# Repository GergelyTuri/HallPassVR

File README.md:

# HallPassVR
## Virtual reality system for head-fixed mouse experiments. 

See published paper on [JOVE](https://app.jove.com/v/64863/an-open-source-virtual-reality-system-for-the-measurement-of-spatial-learning-in-head-restrained-mice).

We developed an inexpensive, single board computer-based, easy-to-use setup for investigation of mouse spatial learning behavior using a visual virtual reality (VR) environment. This system uses a network of microcontrollers (ESP32) and a Raspberry Pi single-board computer to display a virtual linear track to a headfixed mouse running on a wheel. Along with a custom software package written in Python and C++ to generate parameterized virtual environments, this methodology allows researchers the design of various spatial navigation-based experiments to study neural circuits in the brain underlying spatial behaviors. [Example video here](https://www.youtube.com/watch?v=iCfhJT3dYIo):  

## Main hardware requirements: 
1. _ESP32 microcontrollers_ to track and convert mouse movement on a treadmill or wheel to serial data and to control other harware elements (lick spout for reward delivery).
2. _Raspberry Pi 4_ for building and simulating the virtual reality environment. 
3. _Projector_ for visualizing the virtual corridor.
4. PCB shields through [OpenMaze](https://claylacefield.wixsite.com/openmazehome/openmaze-shields)

## Software requirements: 
1. The virtual corridor was designed with _Python_. 
2. Native, Linux-based OS for Raspberry Pi.
3. _tkinter_ was used for designing the graphical user interface.
4. _Arduino IDE_ for programing the microcontrollers.
5. _Processing_ for data collection and plotting.
6. The analysis of behavior files currently requires _Matlab_.

### What we have done: 
1. We built the main part of the system which can simultaneously run and show the virtual reality environment on a computer display and a projector.
2. We have built a prototype GUI which can be used to build virtual corridors from virtually any kind of jpeg images.
3. We tested the system with several testbenches.

### Work in progress: 
1. Finalizing the code by adding documentation and examples.
                
### Future plans: 
1. Optimization of the system by e.g., adding an RFID sensor to increase wheel tracking accuracy.
3. Adding other features to the VR software like naturalistic scenes, looming stimulus or cliff-like effects. 
4. Implementing the analysis scripts in Python.
5. Increasing the flexibility of the existing protocols. 
6. Implementing a wireless (e.g., bluetooth) system using this platform.
## Quickstart:
### Initializing VR environment: 

1. Open a terminal window in Raspberry Pi and navigate to the `HallPassVR` folder
 ```bash
cd /home/pi/Documents/HallPassVR
 ```
2. Starting the VR GUI:
```bash
python3 HallPassVR_GUI.py
 ```
3. Setting up the floors and corridors in the GUI
4. Setting up `Processing` sketch to acquire and plot behavior.
5. Preliminary analysis of the acquired data can be done in Matlab with the scripts in `/Analysis code` folder.

#### GUI: 

#### Example virtual corridor: 

For feature requests, support or questions, please open a ticket on [GitHub](https://github.com/GergelyTuri/mouseVR/issues).

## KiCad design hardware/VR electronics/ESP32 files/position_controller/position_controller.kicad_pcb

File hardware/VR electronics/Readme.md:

# Instructions for the electronic components

Files in the `ESP32 files` directory should be uploaded to the ESP32 boards connected to the lickport and rotary encoder. 

Files in `/PCBs` can get manufatured with companies specialized to PCB production. Typically we use [OSH Park](https://oshpark.com/) if we don't want to modify the design. More info on how to order and assemble these shields can be found on [OpenMaze](http://www.openmaze.org/).

| material | description | source |
| -------- | ----------- | ------ |
| Raspberry Pi 4 model B | single-board computer | e.g., raspberrypi.com, adafruit.com |
| rotary encoder | ENS1J-B28-L00256L | digikey.com[^1] |
|ESP32 devKitC v4 | microcontroller (x2)| e.g., [Amazon.com](https://www.amazon.com/s?k=ESP32&crid=ZCZ3J597DJO9&sprefix=esp32%2Caps%2C94&ref=nb_sb_noss_1)|
|OpenMaze OMwESP32 shield| custom design | see: `/PCBs` folder |

[^1]: Alternative sources: amazon.com, mouser.com, DigiPart, etc.

## Installation instructions for Raspberry Pi:
### Configure RaspberryPi 4 model B 
This single-board computer has an onboard GPU to facilitate VR environment rendering, as well as two HDMI ports for experiment control/monitoring and VR projection.
1. Download Raspberry Pi Imager app and install OS (currently RaspberryPi OS r.2021-05-07) on microSD card (8GB+), insert and boot Raspberry Pi.
2. Configure Raspberry Pi: (menu bar) 
- `Preferences>Raspberry Pi Configuration>`
  - `Display>Screen Blanking>Disable`
  - `Interfaces>Serial Port>Enable` 
  - `Performance>GPU Memory>256`
3. In the terminal: 
``` bash
sudo nano /boot/config.txt
``` 
then uncomment `config_hdmi_boost=4`. Save, reboot the Raspberry Pi.

4. Download and install Arduino IDE from arduino.cc/en/software (e.g. arduino-1.8.19-linuxarm.tar.gz)
5. Download and install Processing IDE from github.com/processing/processing4/releases (e.g. processing-4.0.1-linux-arm32.tgz)
6. In the terminal
```bash
sudo pip3 install pillow –-upgrade
```
7. Then, 
```bash
sudo pip3 install pi3d
```
8. Install ESP32 support on Arduino IDE.

## Set up rotary encoder-ESP32 connections
1. Connect wires between rotary encoder and ESP32.
2. Connect serial RX/TX wires between ESP32 Serial2 (pins 16,17) and behavior ESP32.
3. Connect serial RX/TX wires between ESP32 Serial0 (RX/TX) and Raspberry Pi GPIO (or direct USB connection).
4. Set up behavior ESP32 connections with behavioral hardware (via OMwESP32small PCB).
5. Connect 12V liquid solenoid valve to ULN2803 IC output (e.g. pin#32).
6. Connect lick port to ESP32 touch inputs (e.g. T2, GPIO15).
7. Connect serial RX/TX wires between behav ESP32 Serial2 (pins 16,17) and rotary encoder ESP32 (see above #1.b.).
8. Plug USB into Raspberry Pi USB port (or other PC running Processing to capture behavior data).
9. Plug Raspberry Pi HDMI #2 output into projector HDMI port.

## Set up software (rotary encoder ESP32 and behavior ESP32 w. OM PCB)
1. Plug rotary encoder ESP32 into Raspberry Pi USB port first- it will be automatically be named `/dev/ttyUSB0`
2. Load rotary encoder arduino code by first selecting the ESP32 under `Arduino IDE>Tools>Boards>ESP32 Dev Module`, then `Tools>Port`>`/dev/ttyUSB0`, then click `Upload`: `RotaryEncoder_Esp32_VR.ino`
3. Plug behavior ESP32 into Raspberry Pi USB port next- it will be named `/dev/ttyUSB1`
4. Load behavior sequence arduino code (ESP32 Dev Module already selected), then `Tools>Port>` `/dev/ttyUSB1`, then click `Upload`: `wheel_VR_behavior.ino`
5. You can test serial connections by selecting the Port in the Arduino IDE, then clicking on `Tools>Serial Monitor` (baud rate:115200), to observe serial output from the rotary board (USB0) or the behavior board (USB1).
6. Download HallPassVR python code from this GitHub repo (`/software/HallPassVR`) to `/home/pi/Documents`.

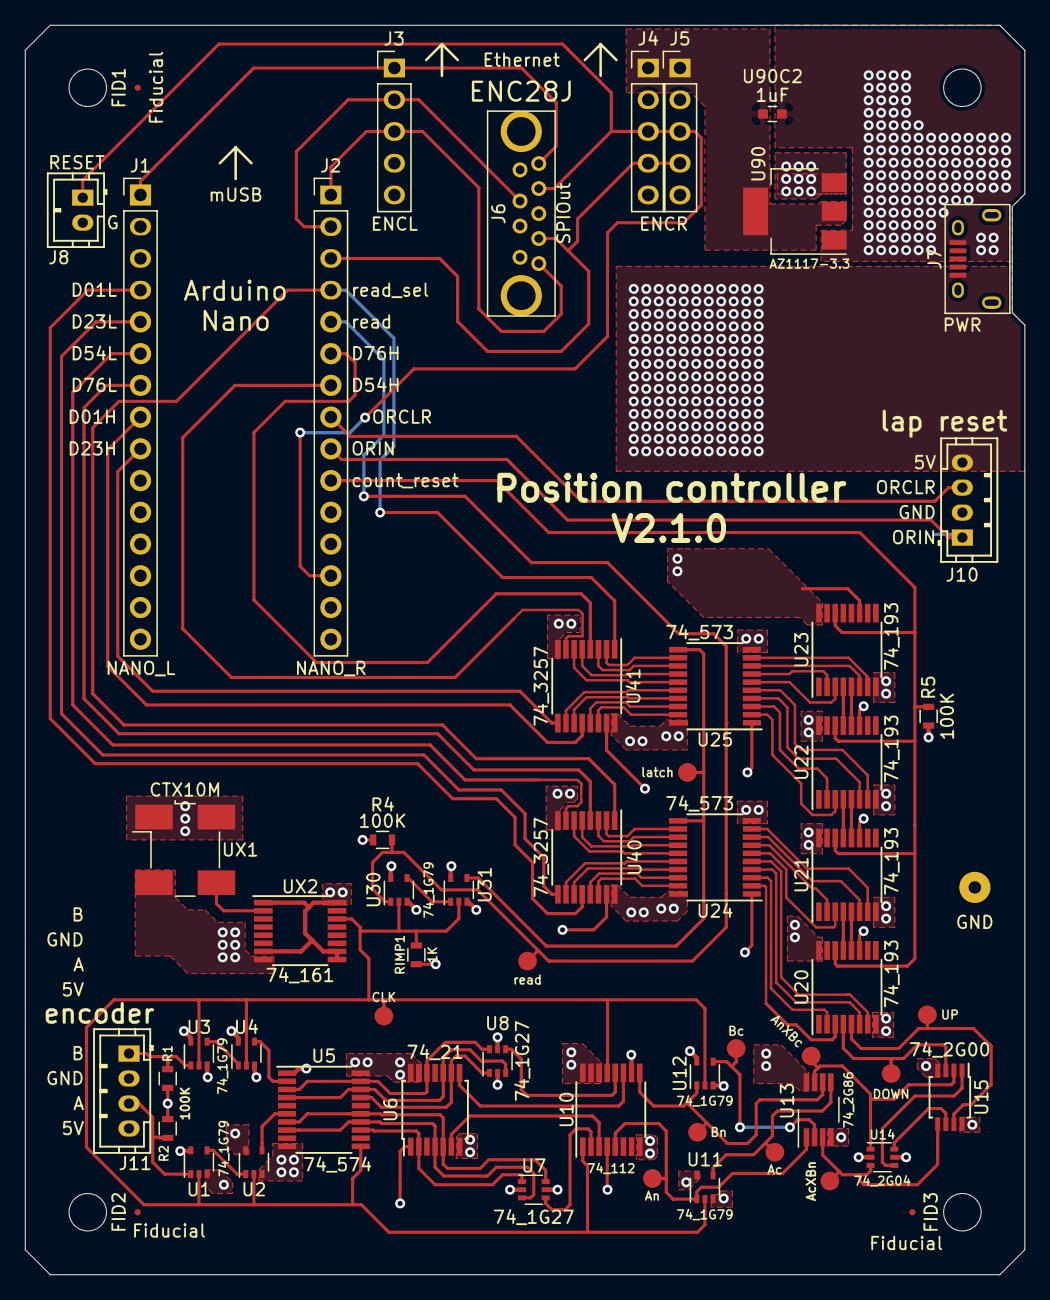
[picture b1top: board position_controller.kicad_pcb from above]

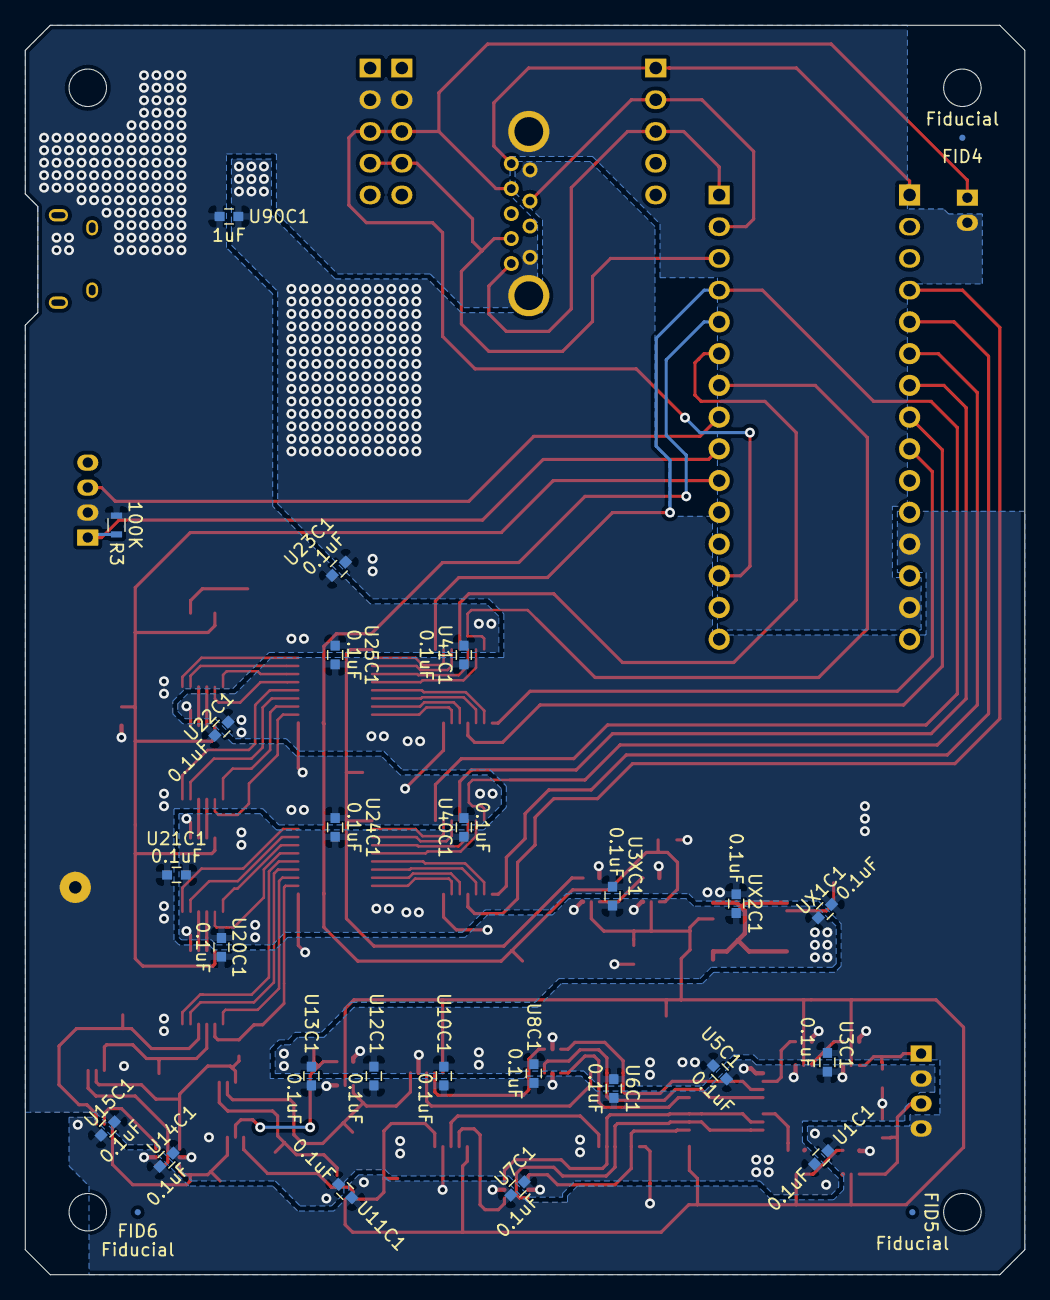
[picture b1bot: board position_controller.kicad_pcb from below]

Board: 2 copper layers, 80.0 x 100.0 mm, 86 parts (28 on the bottom side), 89 nets.

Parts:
FID1, FID2, FID3, FID4, FID5, FID6: Fiducial; Fiducial_0.5mm_Dia_1mm_Outer
J1: NANO_L; Pin_Header_Straight_1x15_Pitch2.54mm
J2: NANO_R; Pin_Header_Straight_1x15_Pitch2.54mm
J3: ENCL; Pin_Header_Straight_1x05_Pitch2.54mm
J4: ENCR; Pin_Header_Straight_1x05_Pitch2.54mm
J5: ENCRW; Pin_Header_Straight_1x05_Pitch2.54mm
J6: SPIOut; USB3_A_vertical_molex
J7: PWR; USB_Micro-B
J8: RESET; Connectors_JST_B2B-PH-K
J10: lap reset; Connectors_JST_B4B-PH-K
J11: encoder; Connectors_JST_B4B-PH-K
R1, R2, R3, R4, R5: 100K; R_0603
RIMP1: 1K; R_0603
TAc1: Ac; Measurement_Point_Round-SMD-Pad_Small
TAcXBn1: AcXBn; Measurement_Point_Round-SMD-Pad_Small
TAn1: An; Measurement_Point_Round-SMD-Pad_Small
TAnXBc1: AnXBc; Measurement_Point_Round-SMD-Pad_Small
TBc1: Bc; Measurement_Point_Round-SMD-Pad_Small
TBn1: Bn; Measurement_Point_Round-SMD-Pad_Small
TCLK1: CLK; Measurement_Point_Round-SMD-Pad_Small
TDN1: DOWN; Measurement_Point_Round-SMD-Pad_Small
TLatch1: latch; Measurement_Point_Round-SMD-Pad_Small
TPGND1: GND; Measurement_Point_Round-TH_Big
TRead1: read; Measurement_Point_Round-SMD-Pad_Small
TUP1: UP; Measurement_Point_Round-SMD-Pad_Small
U1, U2, U3, U4, U11, U12, U30, U31: 74_1G79; SOT-353_SC-70-5
U1C1, U3C1, U3XC1, U5C1, U6C1, U7C1, U8C1, U10C1, U11C1, U12C1, U13C1, U14C1, U15C1, U20C1, U21C1, U22C1, U23C1, U24C1, U25C1, U40C1, U41C1: 0.1uF; C_0603
U5: 74_574; TSSOP-20_4.4x6.5mm_Pitch0.65mm
U6: 74_21; TSSOP-14_4.4x5mm_Pitch0.65mm
U7, U8: 74_1G27; SOT-363_SC-70-6
U10: 74_112; TSSOP-16_4.4x5mm_Pitch0.65mm
U13: 74_2G86; VSSOP-8_3.0x3.0mm_Pitch0.65mm
U14: 74_2G04; SOT-363_SC-70-6
U15: 74_2G00; TSSOP-8_3x3mm_Pitch0.65mm
U20, U21, U22, U23: 74_193; TSSOP-16_4.4x5mm_Pitch0.65mm
U24, U25: 74_573; TSSOP-20_4.4x6.5mm_Pitch0.65mm
U40, U41: 74_3257; TSSOP-16_4.4x5mm_Pitch0.65mm
U90: AZ1117-3.3; SOT-223-3_TabPin2
U90C1, U90C2: 1uF; C_0603
UX1: CTX10M; Oscillator_SMD_Abracon_ASV-4pin_7.0x5.1mm_HandSoldering
UX1C1, UX2C1: 0.1uF; C_0603
UX2: 74_161; TSSOP-16_4.4x5mm_Pitch0.65mm

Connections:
+3V3: J4.1, J5.1, U90.2, U90C2.2
/A: J11.3, R2.1, U1.1
/AQ0: U5.7, U5.15, U6.5, U7.6
/AQ1: U5.8, U5.14, U6.4, U7.3
/AQ2: U5.13, U6.2, U7.1
/Ac: TAc1.1, U11.4, U13.5
/An: TAn1.1, U10.5, U11.1, U13.1
/Async: U2.4, U5.6
/B: J11.1, R1.1, U3.1
/BQ0: U5.3, U5.19, U6.12, U8.6
/BQ1: U5.4, U5.18, U6.10, U8.3
/BQ2: U5.17, U6.9, U8.1
/Bc: TBc1.1, U12.4, U13.2
/Bn: TBn1.1, U10.9, U12.1, U13.6
/Bsync: U4.4, U5.2
/C0H: U22.3, U25.2
/C0L: U20.3, U24.2
/C1H: U22.2, U25.3
/C1L: U20.2, U24.3
/C2H: U22.6, U25.4
/C2L: U20.6, U24.4
/C3H: U22.7, U25.5
/C3L: U20.7, U24.5
/C4H: U23.3, U25.6
/C4L: U21.3, U24.6
/C5H: U23.2, U25.7
/C5L: U21.2, U24.7
/C6H: U23.6, U25.8
/C6L: U21.6, U24.8
/C7H: U23.7, U25.9
/C7L: U21.7, U24.9
/CLK: RIMP1.2, TCLK1.1, U1.2, U2.2, U3.2, U4.2, U5.11, U10.1, U10.13, U11.2, U12.2, U30.2, U31.2, UX2.14
/D0H: U25.19, U41.14
/D0L: U24.19, U40.14
/D01H: J1.8, U41.12
/D1H: U25.18, U41.13
/D01L: J1.4, U40.12
/D1L: U24.18, U40.13
/D2H: U25.17, U41.11
/D2L: U24.17, U40.11
/D3H: U25.16, U41.10
/D3L: U24.16, U40.10
/D4H: U25.15, U41.6
/D4L: U24.15, U40.6
/D5H: U25.14, U41.5
/D5L: U24.14, U40.5
/D6H: U25.13, U41.3
/D6L: U24.13, U40.3
/D7H: U25.12, U41.2
/D7L: U24.12, U40.2
/D23H: J1.9, U41.9
/D23L: J1.5, U40.9
/D54H: J2.7, U41.7
/D54L: J1.6, U40.7
/D76H: J2.6, U41.4
/D76L: J1.7, U40.4
/DOWN: TDN1.1, U15.3, U20.4
/DWT1: U20.13, U21.4
/DWT2: U21.13, U22.4
/DWT3: U22.13, U23.4
/MISO: J2.1, J3.3, J6.5
/MOSI: J2.2, J3.2, J6.2
/ORCLR: J2.8, J10.3
/ORIN: J2.9, J10.1, R3.1
/OSC: UX1.3, UX2.2
/RST: J2.13, J4.3, J5.3, J6.8, J8.1
/SCK: J1.1, J3.1, J6.9
/SPISS: J2.3, J4.4, J5.4, J6.6
/UP: TUP1.1, U15.7, U20.5
/UPT1: U20.12, U21.5
/UPT2: U21.12, U22.5
/UPT3: U22.12, U23.5
/cntRST: J2.10, R5.2, U20.14, U21.14, U22.14, U23.14
/latch: TLatch1.1, U24.11, U25.11, U31.4
/rSel: J2.4, U40.1, U41.1
/read: J2.5, R4.1, TRead1.1, U30.1
GND: J1.14, J4.2, J5.2, J6.4, J6.10, J7.5, J8.2, J10.2, J11.2, R1.2, R2.2, R3.2, R5.1, RIMP1.1, TPGND1.1, U1.3, U1C1.2, U2.3, U3.3, U3C1.2, U3XC1.2, U4.3, U5.1, U5.10, U5C1.2, U6.7, U6C1.2, U7.2, U7C1.2, U8.2, U8C1.2, U10.8, U10C1.2, U11.3, U11C1.2, U12.3, U12C1.2, U13.4, U13C1.2, U14.2, U14C1.2, U15.4, U15C1.2, U20.8, U20C1.2, U21.8, U21C1.2, U22.8, U22C1.2, U23.8, U23C1.2, U24.1, U24.10, U24C1.2, U25.1, U25.10, U25C1.2, U30.3, U31.3, U40.8, U40.15, U40C1.2, U41.8, U41.15, U41C1.2, U90.1, U90C1.1, U90C2.1, UX1.2, UX1C1.2, UX2.8, UX2C1.2
unnamed: TAcXBn1.1, U13.3, U14.3, U15.5
unnamed: TAnXBc1.1, U13.7, U14.1, U15.2
unnamed: U1.4, U2.1
unnamed: U3.4, U4.1
unnamed: U7.4, U10.2
unnamed: U6.6, U10.3
unnamed: U6.8, U10.11
unnamed: U8.4, U10.12
unnamed: U14.4, U15.1
unnamed: U14.6, U15.6
unnamed: U30.4, U31.1
VCC: J1.12, J6.1, J7.1, J10.4, J11.4, R4.2, U1.5, U1C1.1, U2.5, U3.5, U3C1.1, U3XC1.1, U4.5, U5.20, U5C1.1, U6.1, U6.13, U6.14, U6C1.1, U7.5, U7C1.1, U8.5, U8C1.1, U10.4, U10.10, U10.14, U10.15, U10.16, U10C1.1, U11.5, U11C1.1, U12.5, U12C1.1, U13.8, U13C1.1, U14.5, U14C1.1, U15.8, U15C1.1, U20.11, U20.16, U20C1.1, U21.11, U21.16, U21C1.1, U22.11, U22.16, U22C1.1, U23.11, U23.16, U23C1.1, U24.20, U24C1.1, U25.20, U25C1.1, U30.5, U31.5, U40.16, U40C1.1, U41.16, U41C1.1, U90.3, U90C1.2, UX1.1, UX1.4, UX1C1.1, UX2.1, UX2.7, UX2.9, UX2.10, UX2.16, UX2C1.1

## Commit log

2020-09-28 componenst for the old clamp
2020-09-28 headpost
2020-09-30 Create VR_pi3d
2020-09-30 Create Corridor_9272020
2020-10-19 Add files via upload
    Moved roof of corridor. Adding function can randomly creating blue and red corridor
2020-10-19 Rename Silo.py to Silo.py101920
2020-10-23 position controller data added
2021-03-12 Add files via upload
    This is the prototype of the virtual corridor
2021-05-10 Add files via upload
    create listbox with pattern view and scroll bar -5/10/2021
2021-05-10 Add files via upload
    demo of virtual corridor
2021-05-11 Add files via upload
    #1)Fix srollbar
    #2)Fix layout
    #3)Generate Delete_All, Delete, Add, Generate button
    #4)Generate pattern pic
2021-05-12 Add files via upload
    #1) Generate drop menu for combination
    #2) Set combination pattern change Simultaneously
    #3) Add background timer/clean comb list function using thread
    #4) Finish rest 2 combination
2021-05-13 Add files via upload
    #1) Add path canvas
    #2) Add buffer to speed up
    #3) Add read file function to image folder
    #4) Give history, output file
    # --- For Image input ---
    # --- size should be equal or above 5cm x 5cm, file type should be .jpg
2021-05-14 Add files via upload
    #1) Change Layout/Display
    #2) Fix output bug
2021-05-14 Add files via upload
    # --- THIS IS FINAL EDITION FOR NOW FUTURE CHANGE REQUIRED ---
2021-05-17 Add files via upload
    #1) fix serial input issue
    #2) delete mouse control viewing angle and keyboard control function
    #3) test out corridor length corrsponding to 2m path 2m = 4 wheel round 4x100 = 400
    #4) fix GUI trash file issue
2021-05-19 Add files via upload
    First Prototype for Corridor. Bypass bug but need to fix
2021-05-20 Add files via upload
    First System Prototype
2021-05-21 Add files via upload
    #1) Change code outlook
    #2) Fix delete listbox/regenerate bug
2021-05-25 Add files via upload
    #1) Change code outlook
    #2) Fix layout doesn't fit canvas issue
2021-05-25 Add files via upload
    #1) Add listbox/label/canvas for history combination
    #2) generate ouput file for history combination
2021-05-26 Add files via upload
    #1) Finish add/generate history pattern
2021-05-28 Add files via upload
    Finish Delete/Delete All/check function
2021-05-28 patter tiles for the corridor
2021-06-01 Add files via upload
    Usable Version for the VR
2021-06-08 Testbench for GUI
2021-06-11 Least working VR system/ Inside of that : run 6/11
2021-06-17 Add files via upload
    re-design of Encoder using STM32
2021-07-01 Add files via upload
    A working version for demo 7/2
2021-07-08 ESP32_rotary_encoder(delay 25)
2021-07-20 Create mousrVR_bluetooth
2021-07-20 Create bluetooth
2021-07-22 Add files via upload
    ESP32 bluetooth
2021-08-13 Update rfcomm_client2.py
    Use for testing nonblocking Bluetooth Connection
2021-09-12 Refactoring the documentation files
2021-09-12 Correct the text in README.md
2021-09-12 Reorganizing the image files
2021-09-14 Controlling environment via mouse
2021-09-17 Using the mouse to control the environment
2021-09-18 Finish refactoring the virtual reality environment
2021-09-21 Create the VR documentation
    This version contains, (i) a new set of images, and (ii) the code documentation based on the Google Python Style Guide [https://google.github.io/styleguide/pyguide.html]
2021-09-24 Control the VR speed
2021-10-07 Correct the horizontal figures
2021-11-23 Add files via upload
    this version changes : 1)part of logic 2) add self check function 3)output file showing in JSON 4)optimize the speed so far no error exist
    more changes will be made after optimize the outlooking
2022-01-06 Add files via upload
    GUI should be tested in Rasp
2022-01-13 Update Instruction
2022-01-14 Add files via upload
    Old GUI Test file
2022-01-14 old GUI testbench
2022-01-14 ESP32 rotary encoder example
2022-01-14 Bluetooth communicate example
2022-01-14 Img about Corridor implemented on projector
2022-01-14 Working version of Bluetooth/Wired
2022-01-14 Rename Readme to Readme.md
2022-01-14 Instructions about download/install/run the program
2022-09-06 Create Part
2022-09-07 3d model update
2022-09-07 test
2022-09-07 test md
2022-09-14 adding to VR mount
2022-09-14 refactoring, adding new structure
2022-09-14 more refactoring
2022-09-14 modified: README.md
2022-09-16 Add files via upload
    Plate between goniometer and top of running wheel 1x2" aluminum bar.
2022-09-16 metadata hange -- ignore
2022-09-16 new stuff
2022-09-16 webpage stuff
2022-09-16 minor stuff
2022-09-16 minor
2022-09-16 adding analysis folder
2022-09-16 addin some explanations modified: Analysis code/readme.md
2022-09-16 changes in lickport assembly
2022-09-16 adding PCBs
2022-09-16 remove autodate. figure out how to do this.
2022-09-20 Folder
    vr mount folder does not work, and I was not allow to create a new folder outside the existing one so I organize and put everything in the vr head mount folder instead
2022-09-21 minor changes
2022-09-21 embedding video
2022-09-21 refractoring
2022-09-21 correction, new fig for lickport
2022-09-21 corecting typos
2022-09-21 correcting typos
2022-09-21 minor mods
2022-09-23 Add files via upload
    Matlab files for processing VR .txt data (acquired in Processing) and plotting licks by position.
2022-09-23 this is a major refactoring. i deleted the zip file that contained the code so far and added HallPassVR folder which contains the source code. TODO: update install and get started instructions.
2022-09-23 Clay's branch
2022-09-23 temp after trying to merge Clay's branch
2022-09-23 modifying main README file
2022-09-23 correcting typo
2022-09-23 adding two more subfolder for arduino code
2022-09-23 image link correction
2022-09-23 title change
2022-09-26 2D and 3D of wheel and screen
2022-09-26 adding capacitive sensor part num
2022-09-26 modifying a few descriptions.
2022-09-26 Adding electronics setup instructions.
2022-09-26 Add instructions list numbering.
2022-09-26 Adding rotary encoder ESP32 arduino code.
2022-09-26 Adding behavior ESP32 example code.
2022-09-26 Adding MATLAB code for spatial lick analysis.
2022-09-27 adding details
2022-09-27 reorganization and details
2022-09-27 readme-s
2022-09-27 deleting one folder
2022-09-27 adding lik port folder and some other changes
2022-09-27 adding citation cff file
2022-09-28 refactoring, removing VR electronics/ESP32 files
2022-09-28 minor change
2022-09-28 deleting "picture/Default image" and "Additional file" directories
2022-09-30 New gonio/headfix mount plate design.
2022-09-30 Adding OMwSmall gerber .zip file
2022-10-03 New GUI file with frame labels
    Rename to HallPassVR_GUI.py and replace old version
2022-10-04 Annotated wheel laser cut file
2022-10-04 Slight change to annotated wheel laser cut file
2022-11-07 Adding latest VR behavior recording/plotting code
2022-11-07 minor mod
2022-11-07 adding a header to readme for processing code
2022-11-07 aligning github with the info in the JOVE TOM
2022-11-18 adding sample data
2022-11-18 adding some more notes
2022-11-26 black formatting and changes gitignore
2022-11-26 adds requirements.txt
2023-05-19 adding JOVE link to readme
2023-10-25 clean-up
2023-10-25 adding gitignore
2024-06-17 serial comm
2024-06-18 debugging
2024-06-28 new file
2024-07-03 clay updated arduino code
2024-07-03 comments
2025-12-23 Add files via upload
    Straight headpost designs with a 45 angle so it accommodates the arch of the head easier.
